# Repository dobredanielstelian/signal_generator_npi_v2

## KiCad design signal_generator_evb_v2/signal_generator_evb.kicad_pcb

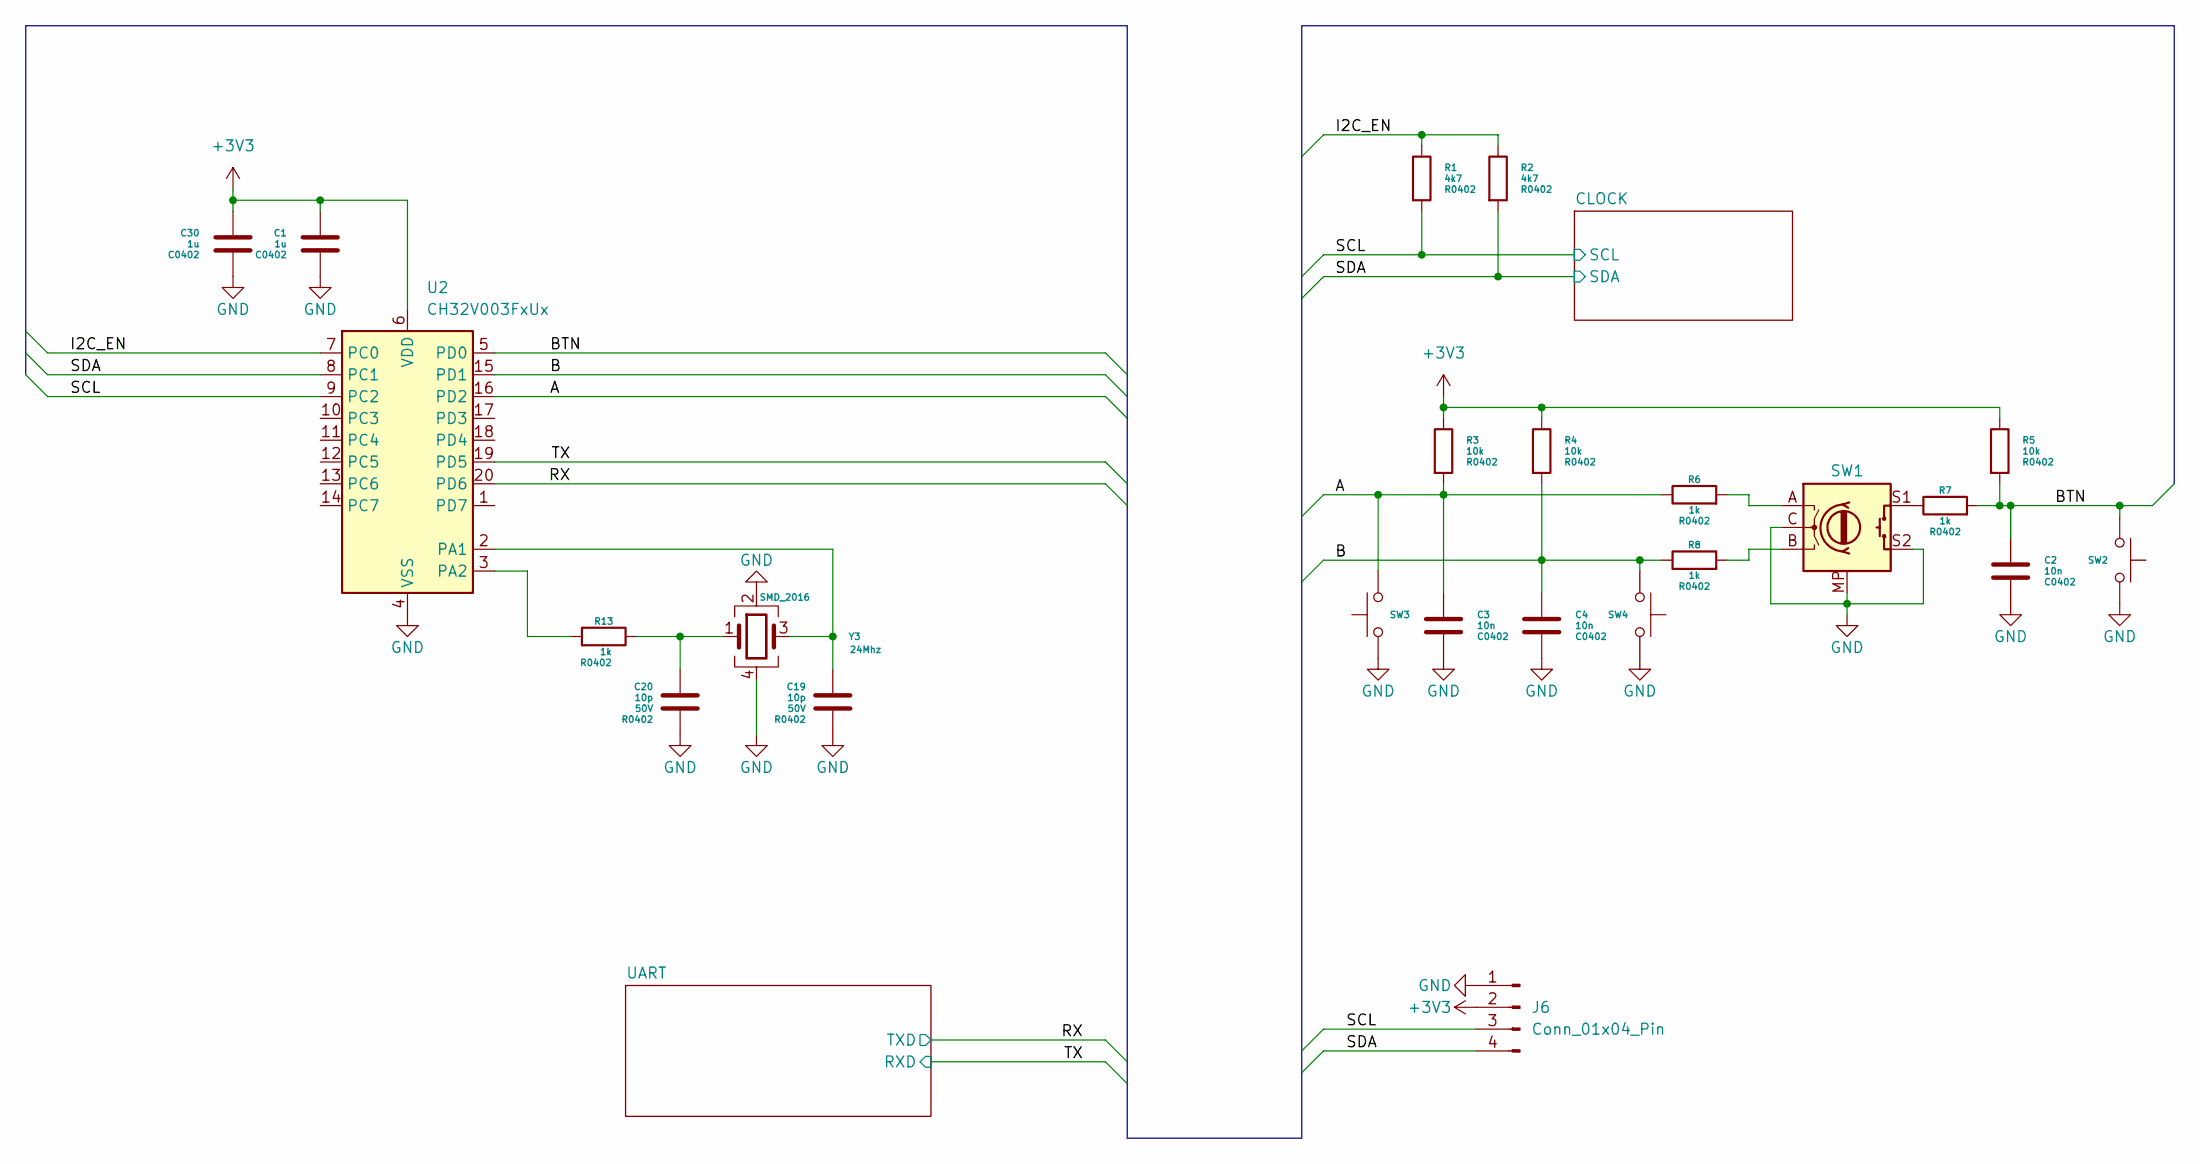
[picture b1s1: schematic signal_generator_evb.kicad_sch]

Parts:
C1, C30: 1u; C_0402_1005Metric
C2, C3, C4: 10n; C_0402_1005Metric
C19, C20: 10p; C_0402_1005Metric
J6: Conn_01x04_Pin; PinHeader_1x04_P2.54mm_Vertical
R1, R2: 4k7; R_0402_1005Metric
R3, R4, R5: 10k; R_0402_1005Metric
R6, R7, R8, R13: 1k; R_0402_1005Metric
SW1: RotaryEncoder_Switch_MP; EC11_SMD
SW2, SW3, SW4: SW_Push; SW_Push_SPST_NO_Alps_SKRK
U2: CH32V003FxUx; QFN-20-1EP_3x3mm_P0.4mm_EP1.65x1.65mm
Y3: 24Mhz; Crystal_SMD_2016-4Pin_2.0x1.6mm

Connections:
+3V3: C1.1, C30.1, J6.2, R3.1, R4.1, R5.1, U2.6 (VDD); also elsewhere on the board
/A: C3.1, R3.2, R6.1, SW3.2, U2.16 (PD2)
/B: C4.1, R4.2, R8.1, SW4.2, U2.15 (PD1)
/BTN: C2.1, R5.2, R7.2, SW2.2, U2.5 (PD0)
/I2C_EN: R1.1, R2.1, U2.7 (PC0)
/RX: U2.20 (PD6); also elsewhere on the board
/SCL: J6.3, R1.2, U2.9 (PC2); also elsewhere on the board
/SDA: J6.4, R2.2, U2.8 (PC1); also elsewhere on the board
/TX: U2.19 (PD5); also elsewhere on the board
GND: C1.2, C2.2, C3.2, C4.2, C19.2, C20.2, C30.2, J6.1, SW1.C, SW1.MP, SW1.S2, SW2.1, SW3.1, SW4.1, U2.4 (VSS), U2.21 (VSS), Y3.2, Y3.4; also elsewhere on the board
unnamed: C20.1, R13.1, Y3.1
unnamed: R6.2, SW1.A
unnamed: R7.1, SW1.S1
unnamed: R8.2, SW1.B
unnamed: C19.1, U2.2 (PA1), Y3.3
unnamed: R13.2, U2.3 (PA2)

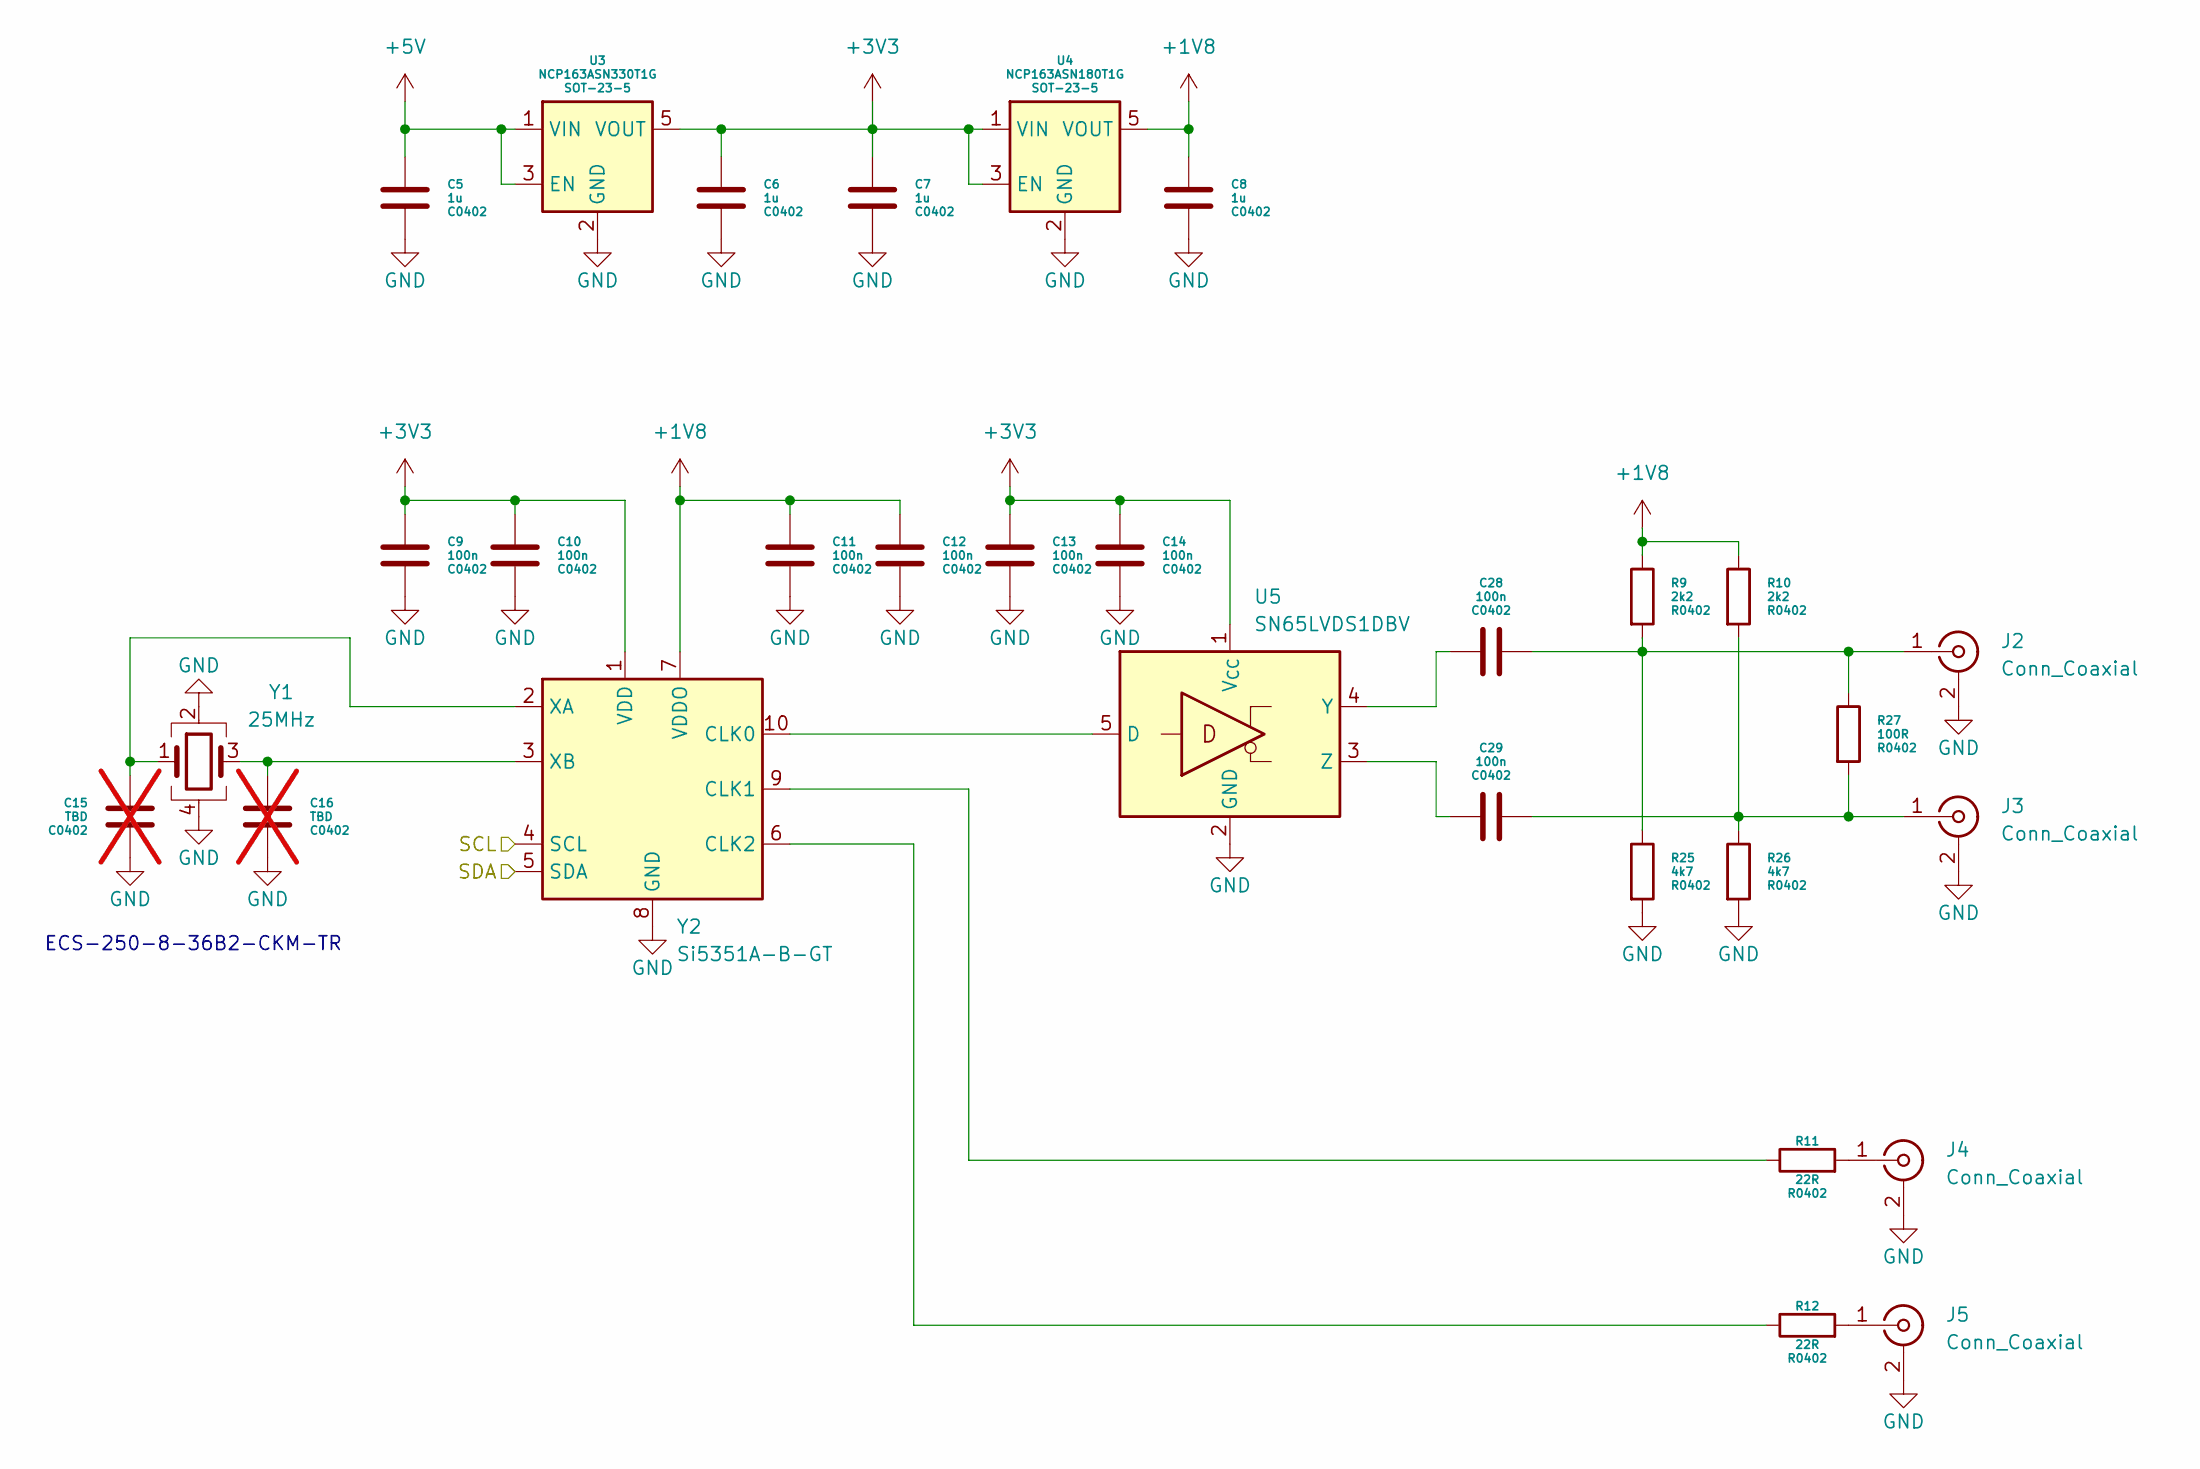
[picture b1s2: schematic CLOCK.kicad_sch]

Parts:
C5, C6, C7, C8: 1u; C_0402_1005Metric
C9, C10, C11, C12, C13, C14, C28, C29: 100n; C_0402_1005Metric
C15, C16: TBD; C_0402_1005Metric; not fitted
J2, J3, J4, J5: Conn_Coaxial; U.FL_Hirose_U.FL-R-SMT-1_Vertical
R9, R10: 2k2; R_0402_1005Metric
R11, R12: 22R; R_0402_1005Metric
R25, R26: 4k7; R_0402_1005Metric
R27: 100R; R_0402_1005Metric
U3: NCP163ASN330T1G; SOT-23-5
U4: NCP163ASN180T1G; SOT-23-5
U5: SN65LVDS1DBV; SOT-23-5
Y1: 25MHz; Crystal_SMD_2016-4Pin_2.0x1.6mm
Y2: Si5351A-B-GT; MSOP-10_3x3mm_P0.5mm

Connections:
+1V8: C8.1, C11.1, C12.1, R9.1, R10.1, U4.5 (VOUT), Y2.7 (VDDO)
+3V3: C6.1, C7.1, C9.1, C10.1, C13.1, C14.1, U3.5 (VOUT), U4.1 (VIN), U4.3 (EN), U5.1 (V_{CC}), Y2.1 (VDD); also elsewhere on the board
+5V: C5.1, U3.1 (VIN), U3.3 (EN); also elsewhere on the board
/SCL: Y2.4 (SCL); also elsewhere on the board
/SDA: Y2.5 (SDA); also elsewhere on the board
GND: C5.2, C6.2, C7.2, C8.2, C9.2, C10.2, C11.2, C12.2, C13.2, C14.2, C15.2, C16.2, J2.2 (Ext), J3.2 (Ext), J4.2 (Ext), J5.2 (Ext), R25.2, R26.2, U3.2 (GND), U4.2 (GND), U5.2 (GND), Y1.2, Y1.4, Y2.8 (GND); also elsewhere on the board
unnamed: C28.2, J2.1 (In), R9.2, R25.1, R27.1
unnamed: C29.2, J3.1 (In), R10.2, R26.1, R27.2
unnamed: J4.1 (In), R11.2
unnamed: J5.1 (In), R12.2
unnamed: U5.5 (D), Y2.10 (CLK0)
unnamed: C28.1, U5.4 (Y)
unnamed: C29.1, U5.3 (Z)
unnamed: R11.1, Y2.9 (CLK1)
unnamed: R12.1, Y2.6 (CLK2)
unnamed: C15.1, Y1.1, Y2.2 (XA)
unnamed: C16.1, Y1.3, Y2.3 (XB)

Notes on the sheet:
ECS-250-8-36B2-CKM-TR

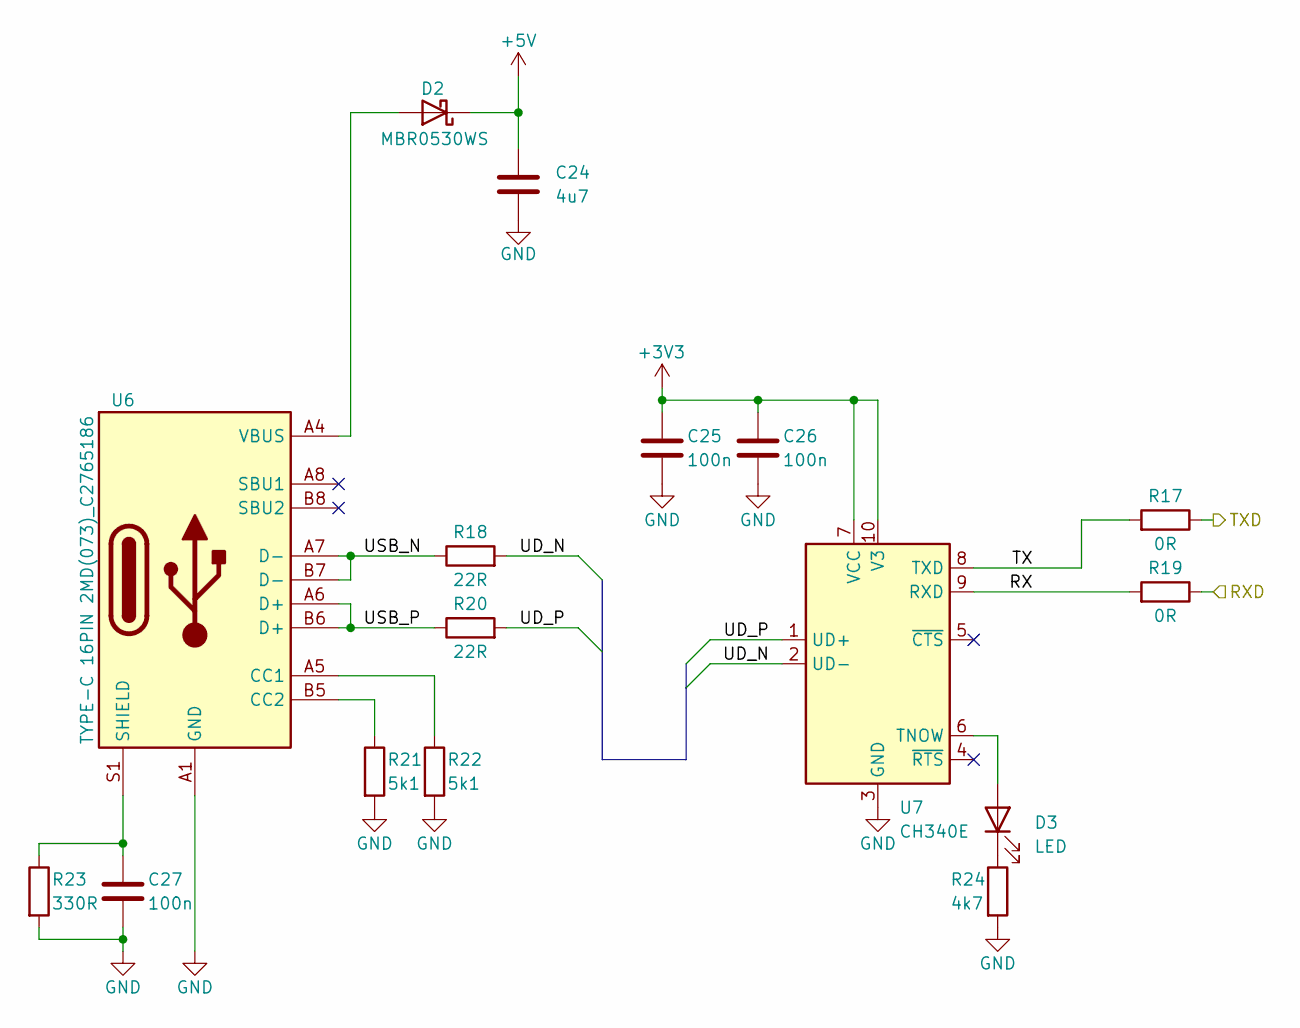
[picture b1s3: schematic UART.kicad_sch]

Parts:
C24: 4u7; C_0402_1005Metric
C25, C26, C27: 100n; C_0402_1005Metric
D2: MBR0530WS; D_SOD-323
D3: LED; D_0402_1005Metric
R17, R19: 0R; R_0402_1005Metric
R18, R20: 22R; R_0402_1005Metric
R21, R22: 5k1; R_0402_1005Metric
R23: 330R; R_0402_1005Metric
R24: 4k7; R_0402_1005Metric
U6: TYPE-C 16PIN 2MD(073)_C2765186; USB_C_Receptacle_Palconn_UTC16-G
U7: CH340E; MSOP-10_3x3mm_P0.5mm

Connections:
+3V3: C25.1, C26.1, U7.7 (VCC), U7.10 (V3); also elsewhere on the board
+5V: C24.1, D2.1 (K); also elsewhere on the board
/RX: R17.1; also elsewhere on the board
/TX: R19.1; also elsewhere on the board
/UART/RX: R19.2, U7.9 (RXD)
/UART/TX: R17.2, U7.8 (TXD)
/UART/UD_N: R18.2, U7.2 (UD-)
/UART/UD_P: R20.2, U7.1 (UD+)
/UART/USB_N: R18.1, U6.A7 (D-), U6.B7 (D-)
/UART/USB_P: R20.1, U6.A6 (D+), U6.B6 (D+)
GND: C24.2, C25.2, C26.2, C27.2, R21.2, R22.2, R23.2, R24.2, U6.A1 (GND), U6.A12 (GND), U6.B1 (GND), U6.B12 (GND), U7.3 (GND); also elsewhere on the board
unnamed: D2.2 (A), U6.A4 (VBUS), U6.A9 (VBUS), U6.B4 (VBUS), U6.B9 (VBUS)
unnamed: D3.2 (A), U7.6 (TNOW)
unnamed: D3.1 (K), R24.1
unnamed: R22.1, U6.A5 (CC1)
unnamed: R21.1, U6.B5 (CC2)
unnamed: C27.1, R23.1, U6.S1 (SHIELD)

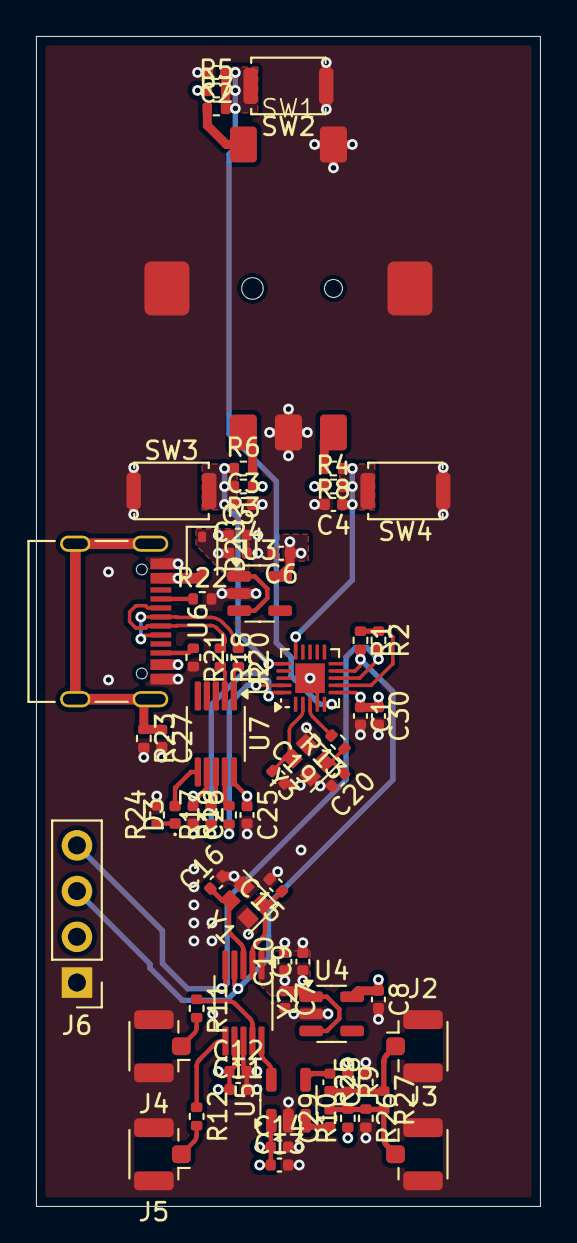
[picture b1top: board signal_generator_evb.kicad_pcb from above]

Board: 4 copper layers, 28.0 x 65.0 mm, 69 parts (0 on the bottom side), 41 nets.

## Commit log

2025-07-30 initial commit 250731_0005
2025-07-31 250801_0030
